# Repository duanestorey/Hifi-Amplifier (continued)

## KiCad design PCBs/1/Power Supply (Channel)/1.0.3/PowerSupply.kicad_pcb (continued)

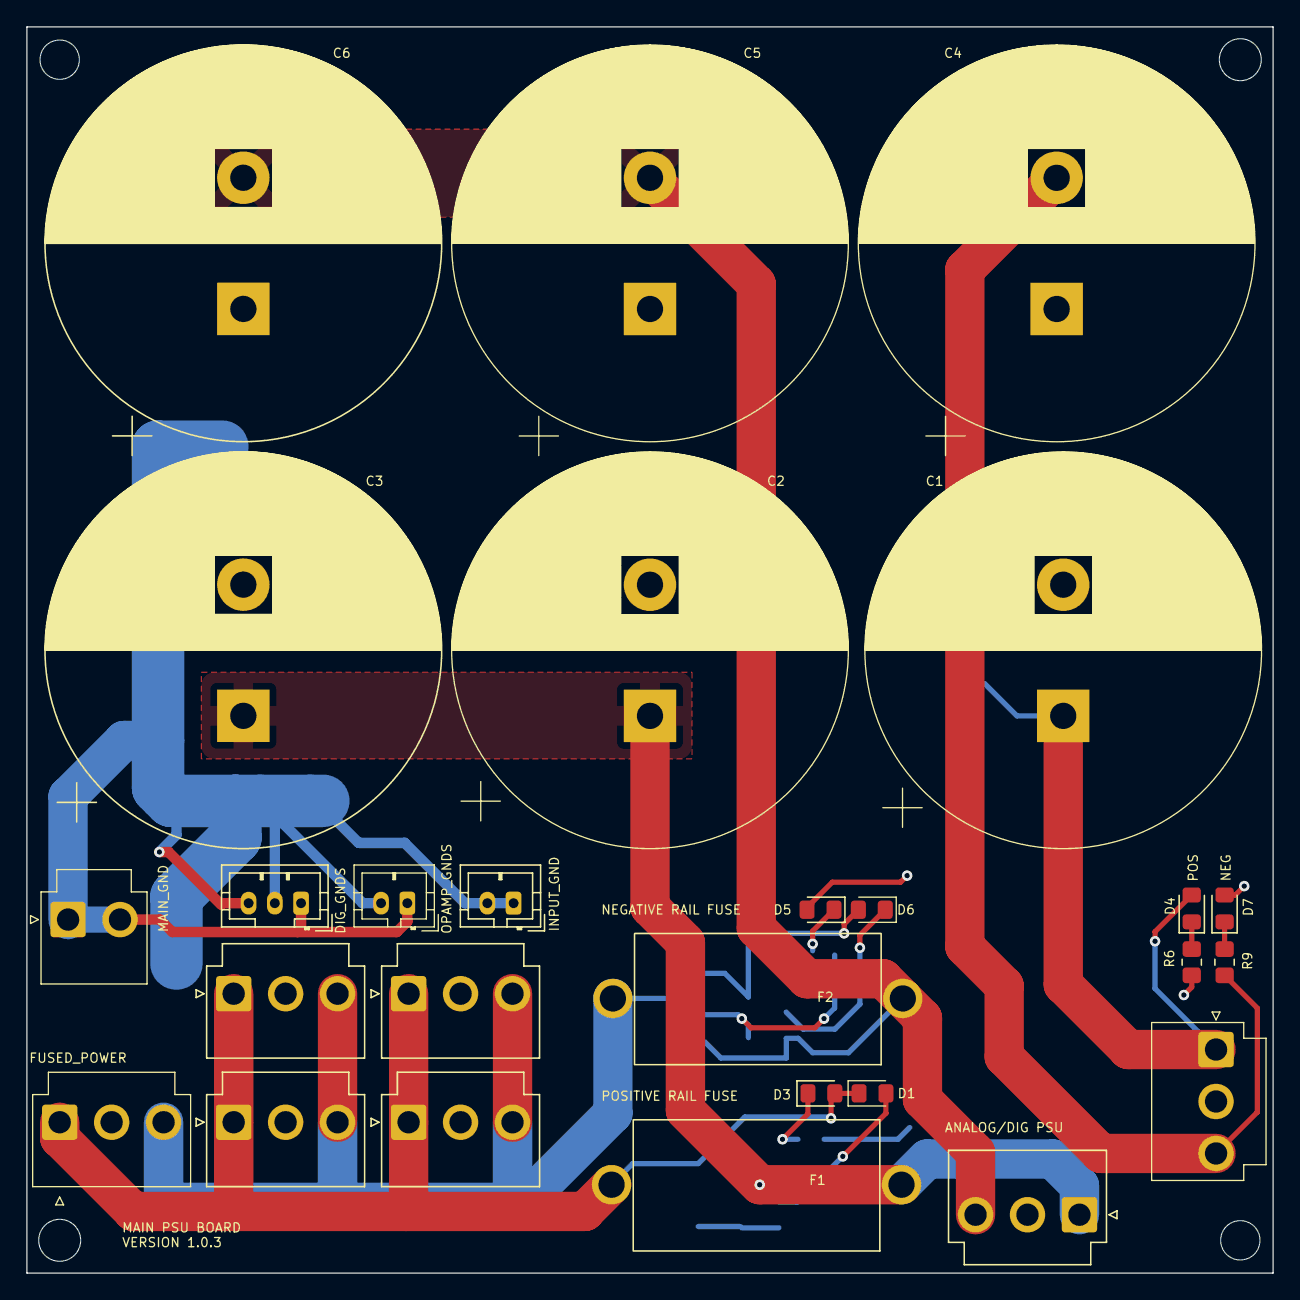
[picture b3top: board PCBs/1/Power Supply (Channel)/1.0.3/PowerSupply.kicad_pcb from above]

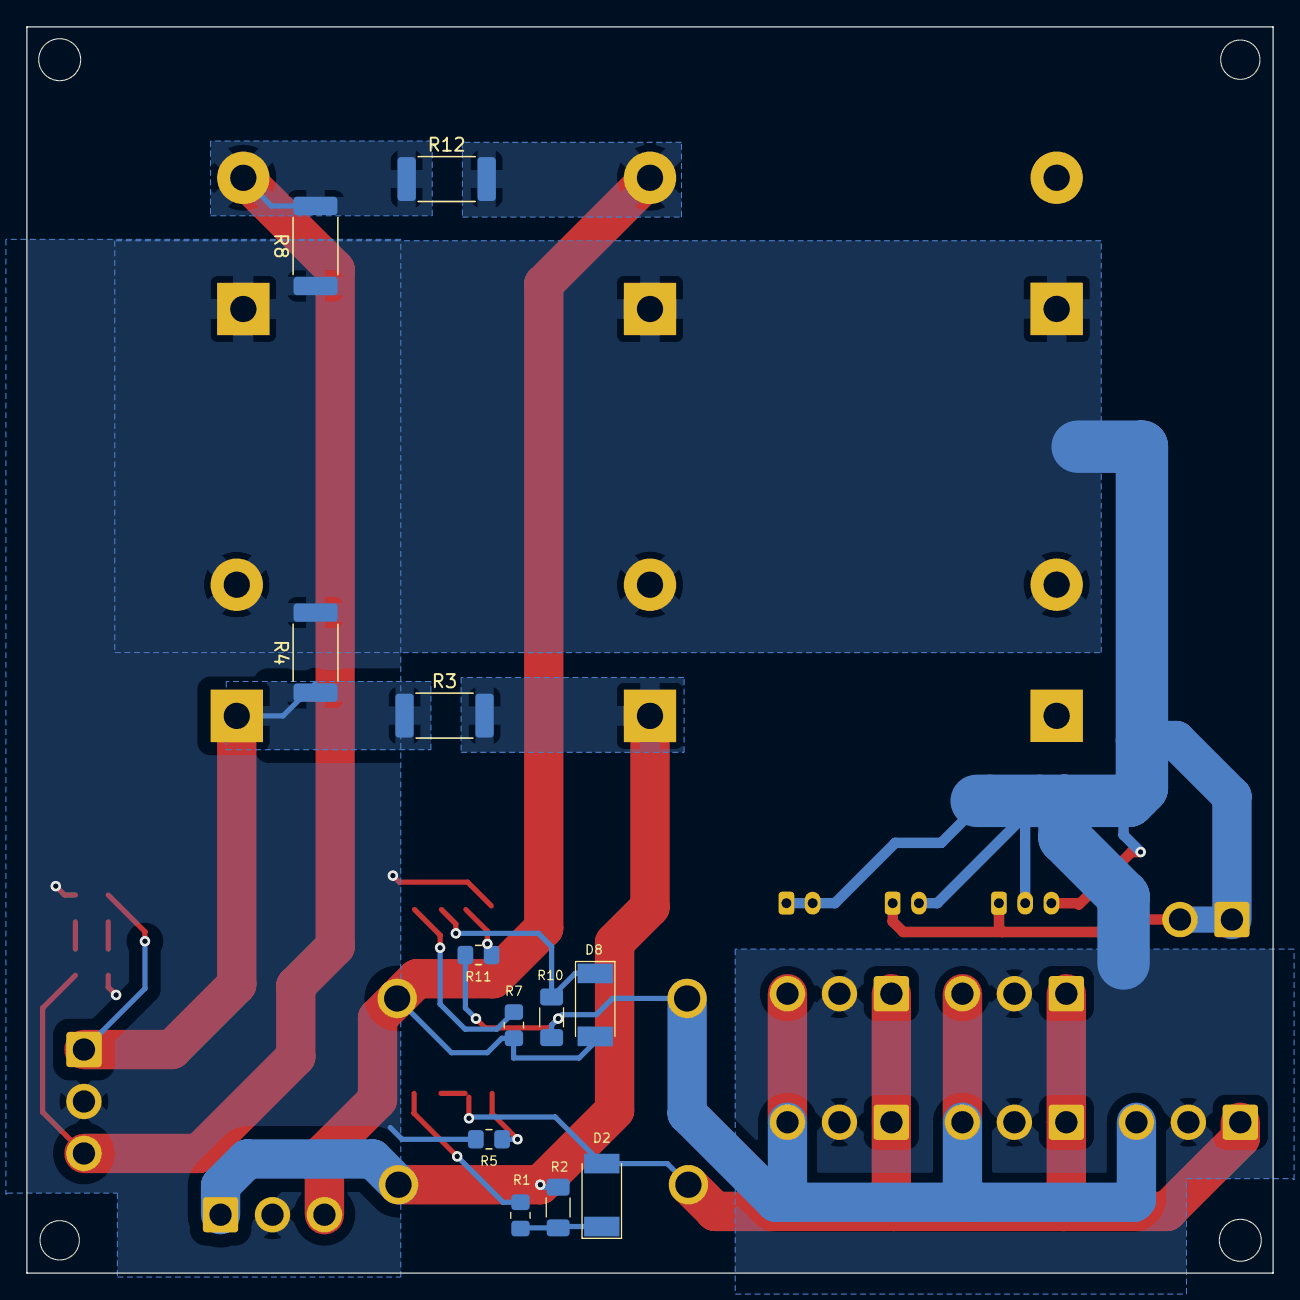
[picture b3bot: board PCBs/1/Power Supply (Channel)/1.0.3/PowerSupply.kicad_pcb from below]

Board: 2 copper layers, 95.0 x 95.0 mm, 43 parts (12 on the bottom side), 15 nets.

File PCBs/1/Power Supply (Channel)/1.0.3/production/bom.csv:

Designator,Footprint,Quantity,Value,LCSC Part #
"C1, C2, C3, C4, C5, C6",CP_Radial_D30.0mm_P10.00mm_SnapIn,6,15000U,
"D1, D6",LED_0805_2012Metric_Pad1.15x1.40mm_HandSolder,2,RED,
"D2, D8",D_MELF,2,5V,
"D3, D4",LED_0805_2012Metric_Pad1.15x1.40mm_HandSolder,2,YELLOW,
"D5, D7",LED_0805_2012Metric_Pad1.15x1.40mm_HandSolder,2,BLUE,
"F1, F2",5x20mm AliExpress 250V 6A,2,Fuse_Small,
"H1, H3",MountingHole_3mm,2,MountingHole,
"H2, H4",MountingHole_3.2mm_M3,2,MountingHole,
"J1, J10, J2, J3, J4, J8, J9",JST_VH_B3P-VH_1x03_P3.96mm_Vertical,7,Conn_01x03_Male,
J11,JST_PH_B3B-PH-K_1x03_P2.00mm_Vertical,1,Conn_01x03_Male,
"J5, J6",JST_PH_B2B-PH-K_1x02_P2.00mm_Vertical,2,Conn_01x02_Male,
J7,JST_VH_B2P-VH-B_1x02_P3.96mm_Vertical,1,Conn_01x02_Male,
"R1, R7",R_0805_2012Metric_Pad1.20x1.40mm_HandSolder,2,560R,
"R10, R2",R_1206_3216Metric_Pad1.30x1.75mm_HandSolder,2,3.5K,
"R11, R5, R6, R9",R_0805_2012Metric_Pad1.20x1.40mm_HandSolder,4,9.1K,
"R12, R3",R_2512_6332Metric_Pad1.40x3.35mm_HandSolder,2,0.050,
"R4, R8",R_2512_6332Metric_Pad1.40x3.35mm_HandSolder,2,1.2K,

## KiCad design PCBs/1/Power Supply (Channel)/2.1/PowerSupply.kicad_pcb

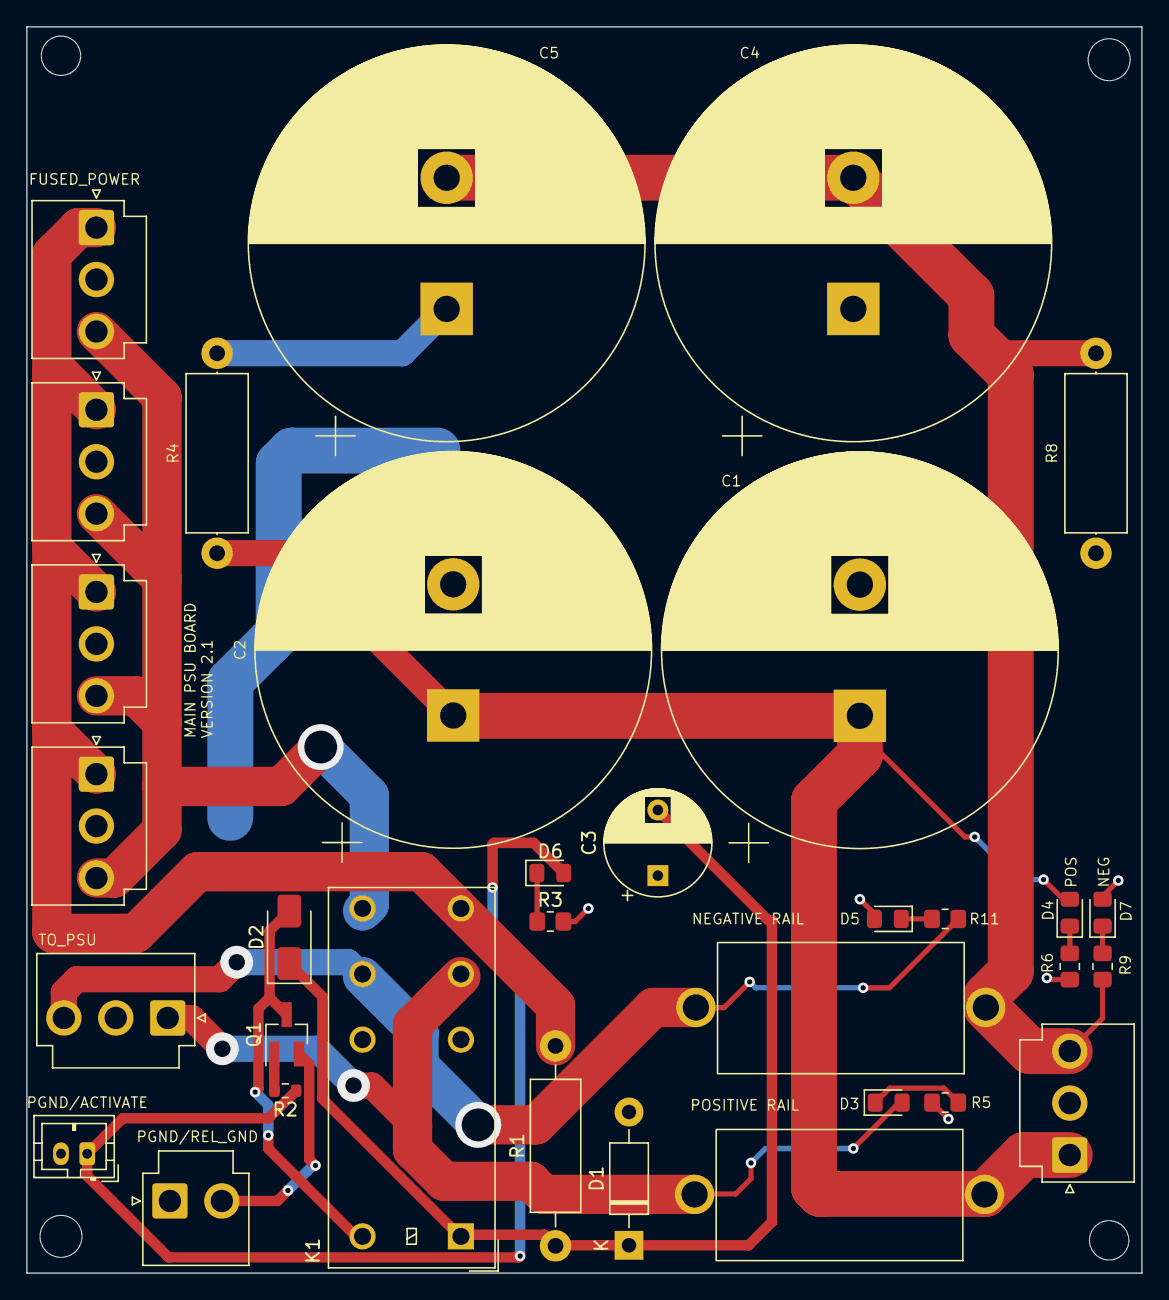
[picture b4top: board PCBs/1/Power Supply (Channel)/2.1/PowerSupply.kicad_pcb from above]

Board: 2 copper layers, 85.0 x 95.0 mm, 37 parts (0 on the bottom side), 17 nets.

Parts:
C1, C2, C4, C5: 15000U; CP_Radial_D30.0mm_P10.00mm_SnapIn
C3: 220u; CP_Radial_D8.0mm_P5.00mm
D1: 12V; D_DO-41_SOD81_P10.16mm_Horizontal
D2: 1N4001; D_SMA
D3, D4: YELLOW; LED_0805_2012Metric_Pad1.15x1.40mm_HandSolder
D5, D7: BLUE; LED_0805_2012Metric_Pad1.15x1.40mm_HandSolder
D6: RED; LED_0805_2012Metric_Pad1.15x1.40mm_HandSolder
F1, F2: Fuse_Small; Aliexpress Fuse 5x20
H1, H3: MountingHole; MountingHole_3mm
H2, H4: MountingHole; MountingHole_3.2mm_M3
J1, J2, J3, J4, J9, J10: Conn_01x03_Male; JST_VH_B3P-VH_1x03_P3.96mm_Vertical
J5: Conn_01x02_Male; JST_PH_B2B-PH-K_1x02_P2.00mm_Vertical
J7: Conn_01x02_Male; JST_VH_B2P-VH-B_1x02_P3.96mm_Vertical
K1: Relay_DPDT; Relay_DPDT_Omron_G2RL-2
Q1: 2SC1945; SOT-23_Handsoldering
R1: 360R 2W; R_Axial_DIN0411_L9.9mm_D3.6mm_P15.24mm_Horizontal
R2: 1K; R_0603_1608Metric
R3: 275R; R_0805_2012Metric_Pad1.20x1.40mm_HandSolder
R4, R8: 1.2K; R_Axial_DIN0414_L11.9mm_D4.5mm_P15.24mm_Horizontal
R5, R6, R9, R11: 9.1K; R_0805_2012Metric_Pad1.20x1.40mm_HandSolder

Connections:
5V: C3.2, D1.1 (K), D2.1 (K), K1.A1, R1.1
ACTIVATE: D6.2 (A), J5.1, R2.1
unnamed: D2.2 (A), K1.A2, Q1.3 (C)
unnamed: D3.1 (K), R5.1
unnamed: D4.1 (K), R6.1
unnamed: D5.1 (K), R11.1
unnamed: D6.1 (K), R3.1
unnamed: D7.1 (K), R9.1
unnamed: Q1.1 (B), R2.2
PGND: C1.2, C2.2, C3.1, C4.1, C5.1, D1.2 (A), D5.2 (A), D7.2 (A), J1.2, J2.2, J3.2, J4.2, J7.1, J9.2, J10.2, R3.2, R4.2, R5.2, R6.2, R8.1
RELAY_GND: J7.2, Q1.2 (E)
VM1: C4.2, C5.2, F2.1, J9.3, R8.2, R9.2
VMOUT: J1.3, J2.3, J4.3, J10.3, K1.24
VMOUT_FUSE: F2.2, J3.3, K1.21, R11.2
VP1: C1.1, C2.1, D4.2 (A), F1.1, J9.1, R4.1
VPOUT: J1.1, J2.1, J4.1, J10.1, K1.14, R1.2
VPOUT_FUSE: D3.2 (A), F1.2, J3.1, K1.11

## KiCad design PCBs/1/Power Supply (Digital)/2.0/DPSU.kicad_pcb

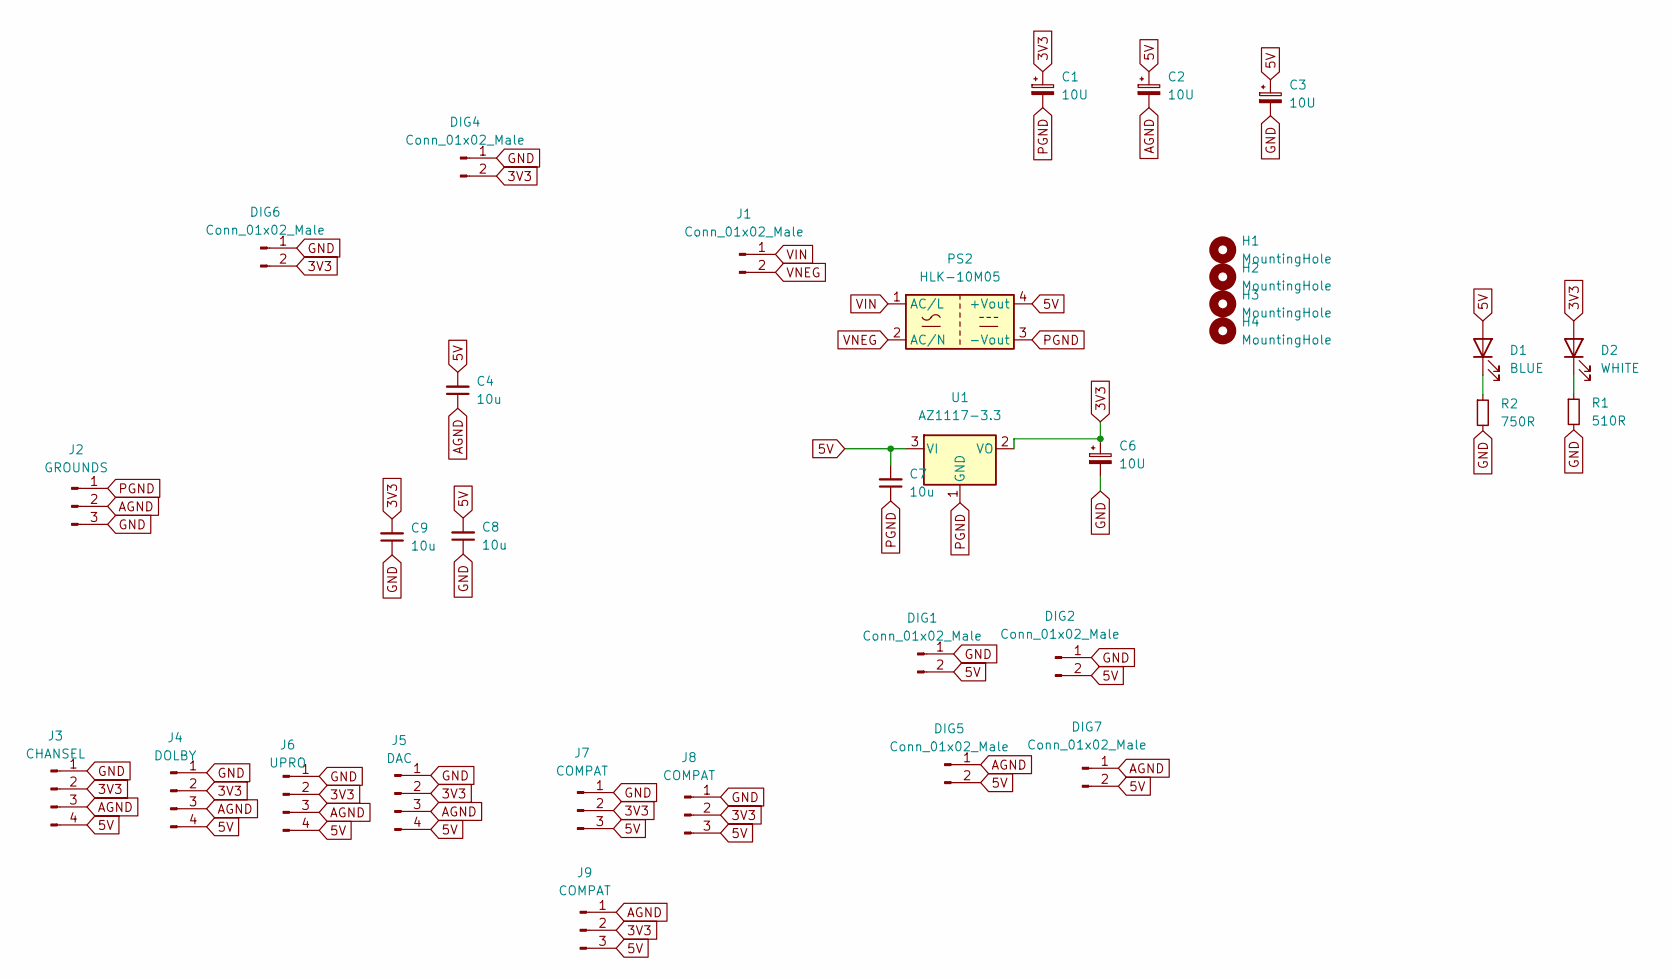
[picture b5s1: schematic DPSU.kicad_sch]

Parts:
C1, C2: 10U; CP_Radial_D8.0mm_P2.50mm
C3, C6: 10U; C_1206_3216Metric_Pad1.33x1.80mm_HandSolder
C4, C7, C8, C9: 10u; C_1206_3216Metric_Pad1.33x1.80mm_HandSolder
D1: BLUE; LED_0805_2012Metric_Pad1.15x1.40mm_HandSolder
D2: WHITE; LED_0805_2012Metric_Pad1.15x1.40mm_HandSolder
DIG1, DIG2, DIG4, DIG5, DIG6, DIG7: Conn_01x02_Male; JST_PH_B2B-PH-K_1x02_P2.00mm_Vertical
H1, H2, H3, H4: MountingHole; MountingHole_3.2mm_M3
J1: Conn_01x02_Male; JST_XH_B2B-XH-A_1x02_P2.50mm_Vertical
J2: GROUNDS; JST_XH_B3B-XH-A_1x03_P2.50mm_Vertical
J3: CHANSEL; JST_PH_B4B-PH-K_1x04_P2.00mm_Vertical
J4: DOLBY; JST_PH_B4B-PH-K_1x04_P2.00mm_Vertical
J5: DAC; JST_PH_B4B-PH-K_1x04_P2.00mm_Vertical
J6: UPRO; JST_PH_B4B-PH-K_1x04_P2.00mm_Vertical
J7, J8, J9: COMPAT; JST_PH_B3B-PH-K_1x03_P2.00mm_Vertical
PS2: HLK-10M05
R1: 510R; R_0805_2012Metric_Pad1.20x1.40mm_HandSolder
R2: 750R; R_0805_2012Metric_Pad1.20x1.40mm_HandSolder
U1: AZ1117-3.3; SOT-223

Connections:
3V3: C1.1, C6.1, C9.2, D2.2 (A), DIG4.2, DIG6.2, J3.2, J4.2, J5.2, J6.2, J7.2, J8.2, J9.2, U1.2 (VO)
5V: C2.1, C3.1, C4.2, C7.2, C8.2, D1.2 (A), DIG1.2, DIG2.2, DIG5.2, DIG7.2, J3.4, J4.4, J5.4, J6.4, J7.3, J8.3, J9.3, PS2.4 (+Vout), U1.3 (VI)
AGND: C2.2, C4.1, DIG5.1, DIG7.1, J2.2, J3.3, J4.3, J5.3, J6.3, J9.1
GND: C3.2, C6.2, C8.1, C9.1, DIG1.1, DIG2.1, DIG4.1, DIG6.1, J2.3, J3.1, J4.1, J5.1, J6.1, J7.1, J8.1, R1.2, R2.2
unnamed: D1.1 (K), R2.1
unnamed: D2.1 (K), R1.1
PGND: C1.2, C7.1, J2.1, PS2.3 (-Vout), U1.1 (GND)
VIN: J1.1, PS2.1 (AC/L)
VNEG: J1.2, PS2.2 (AC/N)

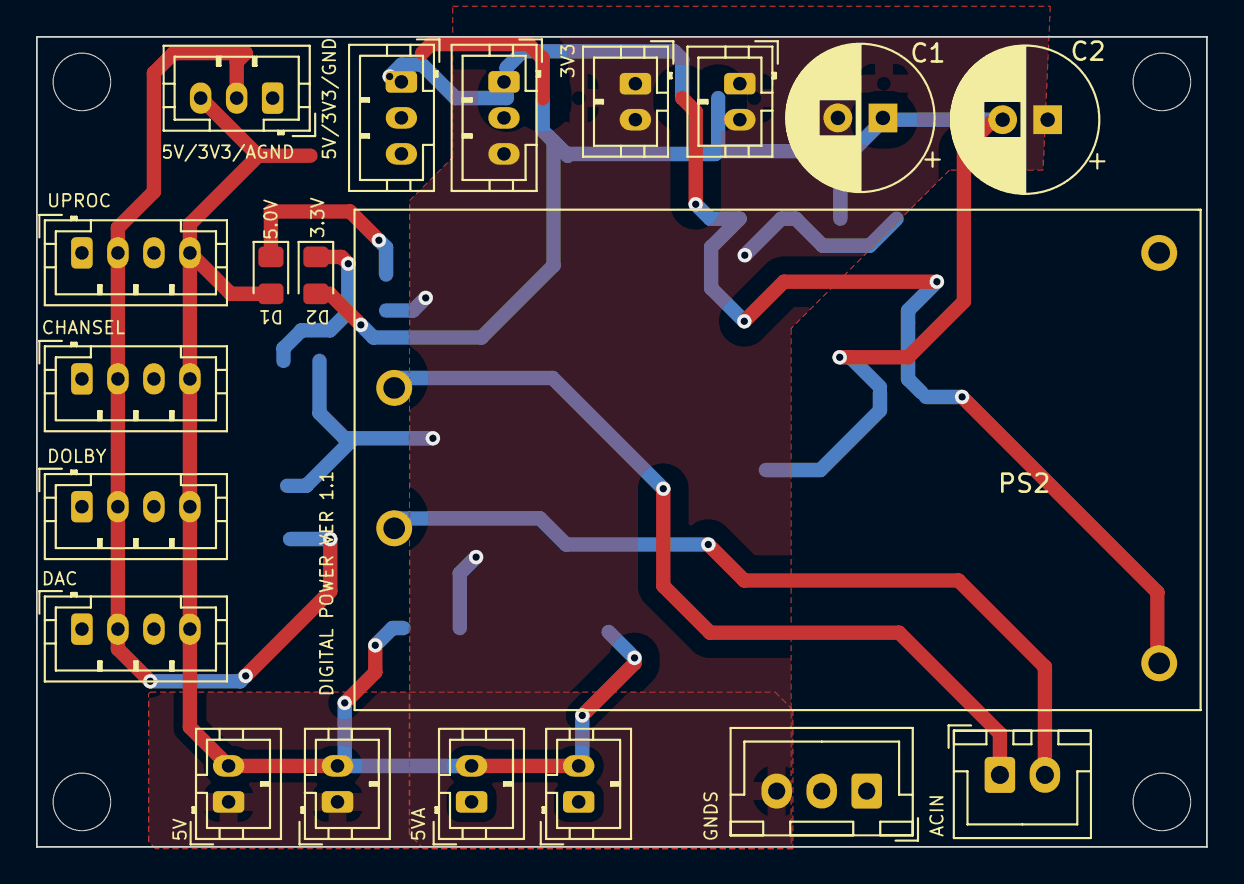
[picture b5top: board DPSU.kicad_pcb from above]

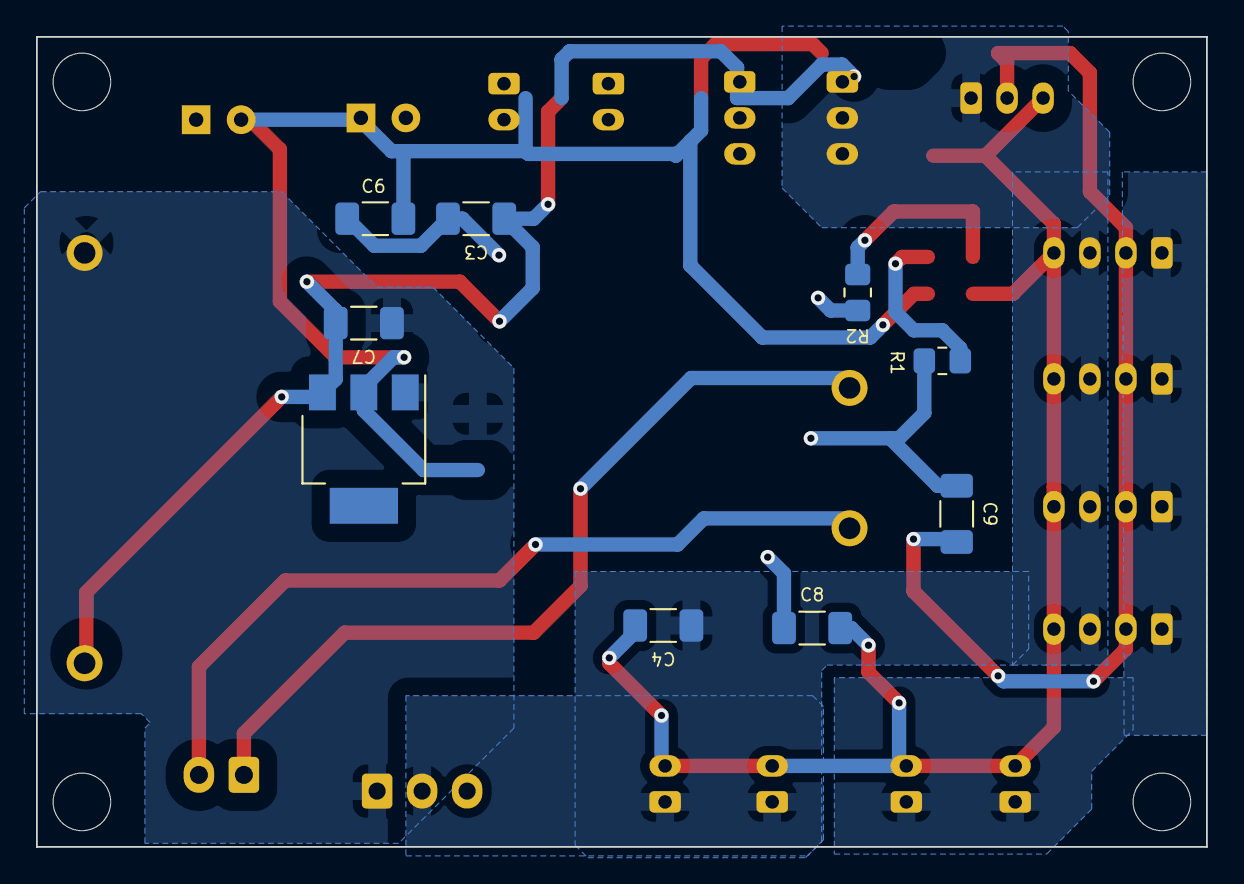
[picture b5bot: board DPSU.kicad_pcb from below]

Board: 2 copper layers, 65.0 x 45.0 mm, 33 parts (9 on the bottom side), 9 nets.
